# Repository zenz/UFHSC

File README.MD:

准备开源一个东西，用来控制地暖系统的。
市场上有类似的产品，但都是闭源的，这个开源，爱折腾爱研究爱写程序的，可以通过这个东西来设计和测试自己的地暖控制逻辑。

包含的接口有：
1、两路温度传感器接口（用B=3950，100K 精度1% NTC电阻温度传感器）
2、一路壁挂炉采暖启停控制接口
3、一路循环泵启停控制接口
4、一路负载式温控面板接口
5、一路温控面板直接控制的热电阀接口
6、一个UART通讯接口，用于通过USB2TTL接线实现与电脑串口通讯
7、一个ICSP接口，用于给单片机刷写Bootloader
8、一个ESP-05款无线WIFI模块接口，用于实现IoT监控
9、一个USB/AC供电跳针接口，用于选择单片机电源供给方式，调试用
10、一个预留的开关判断接口（目前在代码中用于是否连接循环泵的判断）

整个设备，全部采用直插式原件，方便爱好者自己焊接制作。所有用到的零件，都可以在网上（淘宝）购买到。
温度传感器精度可通过选择精度高的NTC电阻以及分压电阻(4.7K)来调节。
目前选用的NTC精度1%，分压电阻精度5%，测试下来在测试物温度恒定时，波动温度不超过0.2度（个人认为对地暖来说这个精度够了，波动更大的原因是开关电源的稳定性）。

单片机采用ATMEL公司的ATMEGA328P-PU，8位处理芯片，FLASH内存32K，动态内存2K，刷开源固件Arduino。
原始控制代码也全部开源，用Arduino编写，在Arduino IDE 1.0.5 以上版本编译通过并可通过USB2TTL上传到单片机。

开源的目的是什么？
个人一直是开源（软硬件）的支持者，认同开源可以使得在开放式讨论环境中，目标理论和算法能够得到更充分的探讨和完善。而且能够在使用环境适应性上有更加灵活的应对方法来解决实际的问题。FDM（熔融堆积成型）三维打印机这几年的发展就是一个例子。还有桌面CNC铣床GBRL，微型纺织机FirePicker等等。Github上随便搜搜都能找到一堆的开源软硬件项目。

开源会不会对企业带来经济损失？
个人认为这是一个伪命题。一个企业的研发能力是有限的，特别是中小型企业，要能够有人员和资金持续地，不断投入一个项目的研究还不钻牛角尖是很难的。因此，很多的企业，甚至是大企业，都采取部分开源的做法，来吸引更多对此问题关注的人参与进来，从而在获得的研究结果中提取有利于企业本身的数据和技术，来不断完善企业自己生产和销售的产品。产品做好了，买来使用的人其实占据了绝大多数。

开源需要的是什么？
开源需要的是真诚的交流和主动改变的心态，在这一点上，国外的开发者似乎比国内的做的要好一些。但这几年，国内的开源项目也多起来了。主要还是心态的慢慢转变吧。

接下来会怎么做？
我会把这个项目放到Github上，所有的设计文件，代码，让有想法又愿意分享并贡献的人可以跟进交流。希望这个开源项目能获得更多人的关注，从而使得对地面辐射采暖节能控制更多的了解和应用。这样我就成功了。如果最后也没有什么进步，那么我也至少努力过了。

OK，我要说的说完了。你约不约？

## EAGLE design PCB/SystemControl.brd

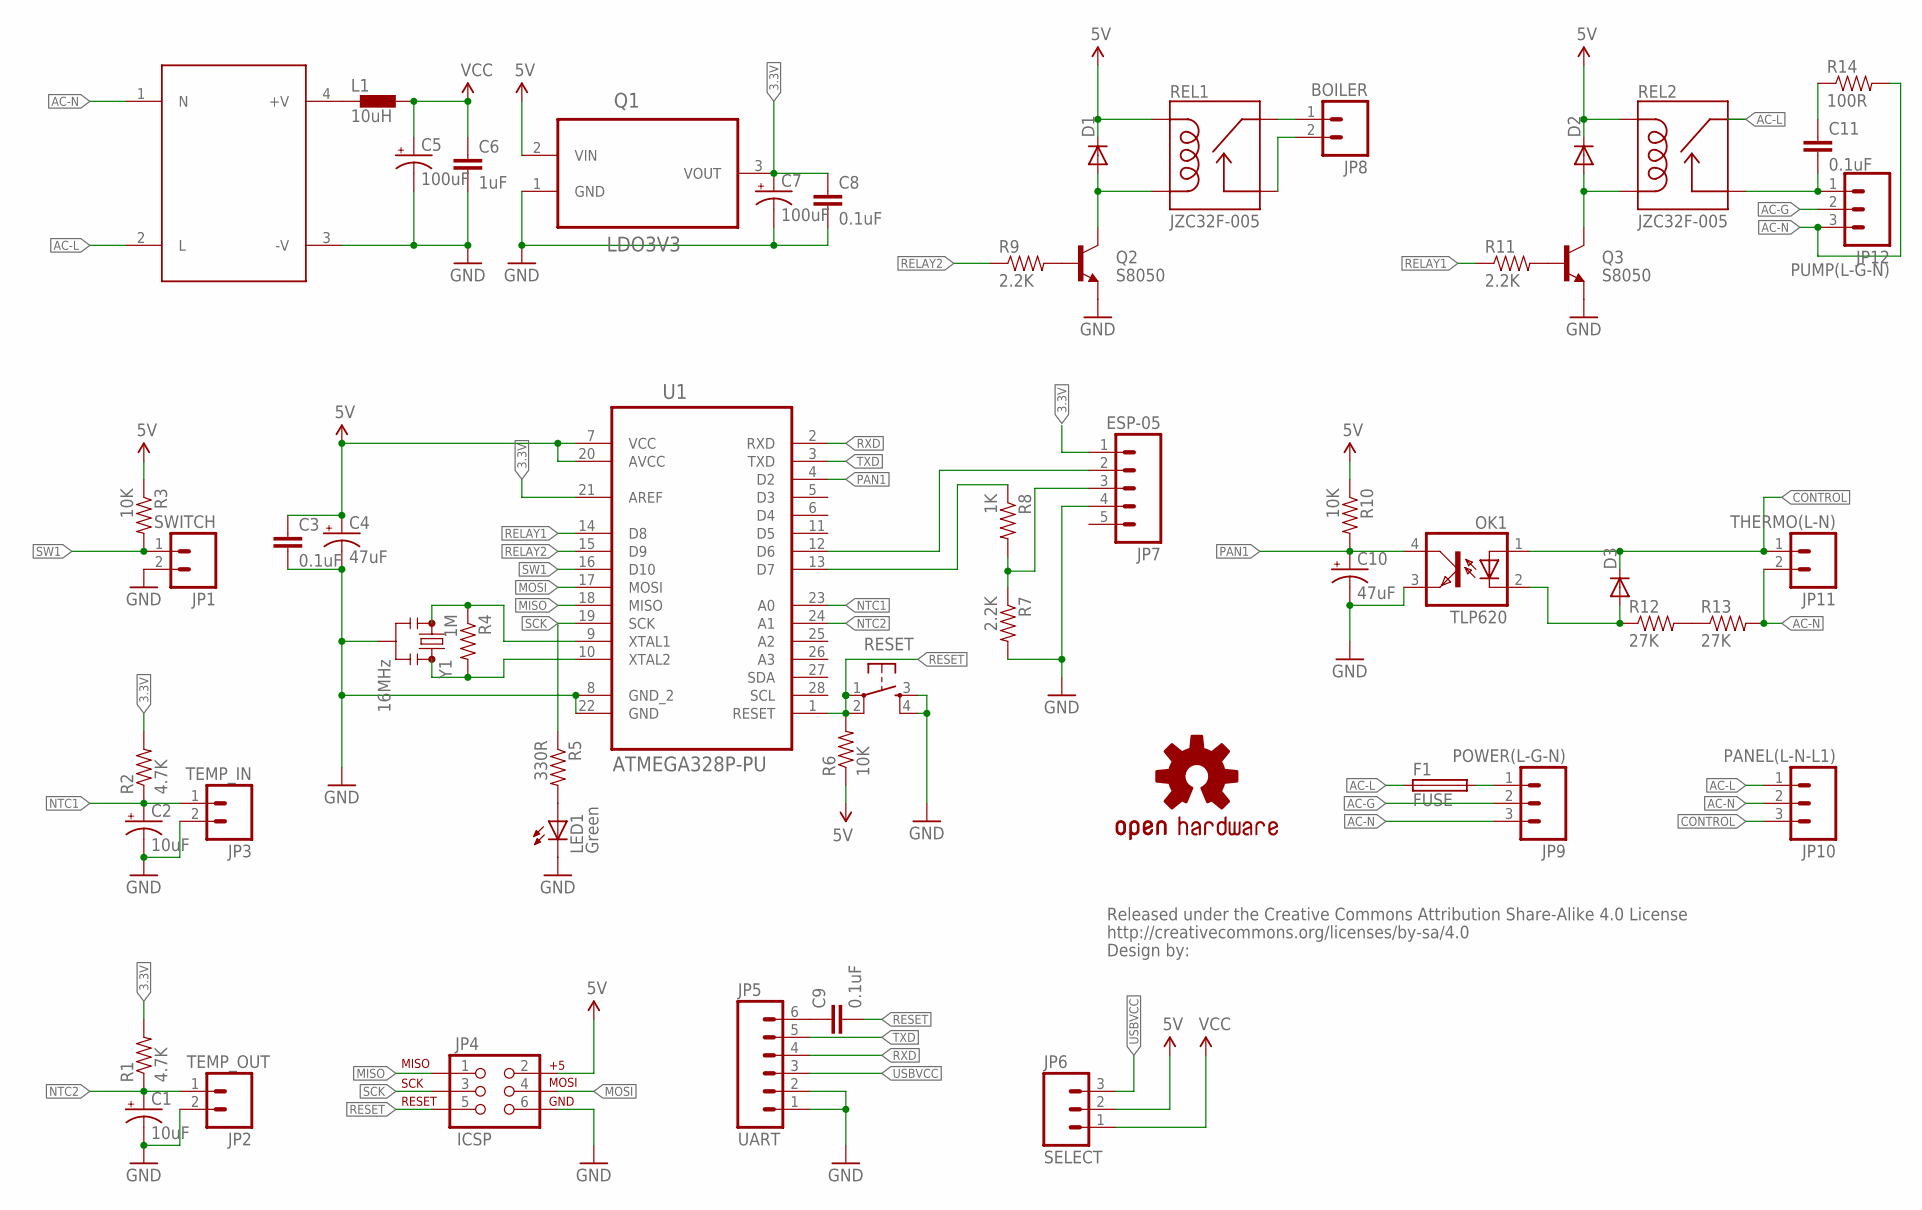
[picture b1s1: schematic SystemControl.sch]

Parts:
C1, C2: 10uF; CPOL-RADIAL-10UF-25V
C3, C8, C9: 0.1uF; CAP-PTH-SMALL2
C4, C10: 47uF; CPOL-RADIAL-10UF-25V
C5, C7: 100uF; CPOL-RADIAL-10UF-25V
C6: 1uF; CAP-PTH-SMALL2
C11: 0.1uF; CAP-PTH-LARGE
CC_TEXT1: CREATIVE_COMMONS
D1, D2, D3: 1N4007; DO-1N4148
F1: FUSE; SHK20L
IC1: NI-BOXING
JP1: SWITCH; 1X02_LOCK
JP2: TEMP_OUT; 1X02_LOCK
JP3: TEMP_IN; 1X02_LOCK
JP4: ICSP; 2X3
JP5: UART; 1X06_LOCK
JP6: SELECT; 1X03_LOCK
JP7: ESP-05; 1X05_LOCK
JP8: BOILER; SCREWTERMINAL-5MM-2
JP9: POWER(L-G-N); SCREWTERMINAL-5MM-3
JP10: PANEL(L-N-L1); SCREWTERMINAL-5MM-3
JP11: THERMO(L-N); SCREWTERMINAL-5MM-2
JP12: PUMP(L-G-N); SCREWTERMINAL-5MM-3
L1: 10uH; BL01RN1A
LED1: Green; LED3MM
LOGO1: OSHW-LOGOL; OSHW-LOGO-L
OK1: TLP620; DIL04
Q1: LDO3V3; TO127P254X533-3
Q2, Q3: S8050; TO-92
R1, R2: 4.7K; AXIAL-0.4
R3, R6, R10: 10K; AXIAL-0.4
R4: 1M; AXIAL-0.4
R5: 330R; AXIAL-0.4
R7, R9, R11: 2.2K; AXIAL-0.4
R8: 1K; AXIAL-0.4
R12, R13: 27K; AXIAL-0.6
R14: 100R; AXIAL-0.6
REL1, REL2: JZC32F-005; RELAY-JZC
RESET: TAC_SWITCHPTH; TACTILE-PTH
U1: ATMEGA328P-PU; DIP254P762X457-28
Y1: 16MHz; RESONATOR-PTH

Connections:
3.3V: C7.1 (+), C8.1, JP7.1, Q1.3 (VOUT), R1.P$2 (2), R2.P$2 (2), U1.21 (AREF)
5V: C3.1, C4.1 (+), D1.C, D2.C, JP4.2 (VCC), JP6.2, Q1.2 (VIN), R3.P$1 (1), R6.P$1 (1), R10.P$1 (1), REL1.5 (COIL1), REL2.5 (COIL1), U1.7 (VCC), U1.20 (AVCC)
AC-G: JP9.2, JP12.2
AC-L: F1.1A (1), IC1.2 (L), JP10.1, REL2.4 (MAIN)
AC-N: IC1.1 (N), JP9.3, JP10.2, JP11.2, JP12.3, R13.P$2 (2), R14.P$2 (2)
CONTROL: D3.C, JP10.3, JP11.1, OK1.1 (A)
GND: C1.2 (-), C2.2 (-), C3.2, C4.2 (-), C5.2 (-), C6.2, C7.2 (-), C8.2, C10.2 (-), IC1.3 (-V), JP1.2, JP2.2, JP3.2, JP4.6 (GND), JP5.1 (GND), JP5.2 (EMPTY), JP7.4, LED1.K (C), OK1.3 (EMIT), Q1.1 (GND), Q2.1 (E), Q3.1 (E), R7.P$2 (2), RESET.3, RESET.4, U1.8 (GND_2), U1.22 (GND), Y1.2
MISO: JP4.1 (MISO), U1.18 (MISO)
MOSI: JP4.4 (MOSI), U1.17 (MOSI)
unnamed: C9.1, JP5.6 (RESET)
unnamed: R4.P$1 (1), U1.9 (XTAL1), Y1.1
unnamed: R4.P$2 (2), U1.10 (XTAL2), Y1.3
unnamed: Q3.2 (B), R11.P$2 (2)
unnamed: D2.A, Q3.3 (C), REL2.1 (COIL2)
unnamed: Q2.2 (B), R9.P$2 (2)
unnamed: D1.A, Q2.3 (C), REL1.1 (COIL2)
unnamed: JP8.1, REL1.4 (MAIN)
unnamed: JP8.2, REL1.3 (NO)
unnamed: LED1.A, R5.P$2 (2)
unnamed: C11.2, JP12.1, REL2.3 (NO)
unnamed: IC1.4 (+V), L1.1
unnamed: C11.1, R14.P$1 (1)
unnamed: JP7.3, R7.P$1 (1), R8.P$2 (2)
unnamed: F1.2A (2), JP9.1
unnamed: R12.P$2 (2), R13.P$1 (1)
unnamed: D3.A, OK1.2 (C), R12.P$1 (1)
unnamed: JP7.2, U1.12 (D6)
unnamed: R8.P$1 (1), U1.13 (D7)
NTC1: C2.1 (+), JP3.1, R2.P$1 (1), U1.23 (A0)
NTC2: C1.1 (+), JP2.1, R1.P$1 (1), U1.24 (A1)
PAN1: C10.1 (+), OK1.4 (COL), R10.P$2 (2), U1.4 (D2)
RELAY1: R11.P$1 (1), U1.14 (D8)
RELAY2: R9.P$1 (1), U1.15 (D9)
RESET: C9.2, JP4.5 (RESET), R6.P$2 (2), RESET.1, RESET.2, U1.1 (RESET)
RXD: JP5.4 (RXD), U1.2 (RXD)
SCK: JP4.3 (SCK), R5.P$1 (1), U1.19 (SCK)
SW1: JP1.1, R3.P$2 (2), U1.16 (D10)
TXD: JP5.5 (TXD), U1.3 (TXD)
USBVCC: JP5.3 (VCC), JP6.3
VCC: C5.1 (+), C6.1, JP6.1, L1.2

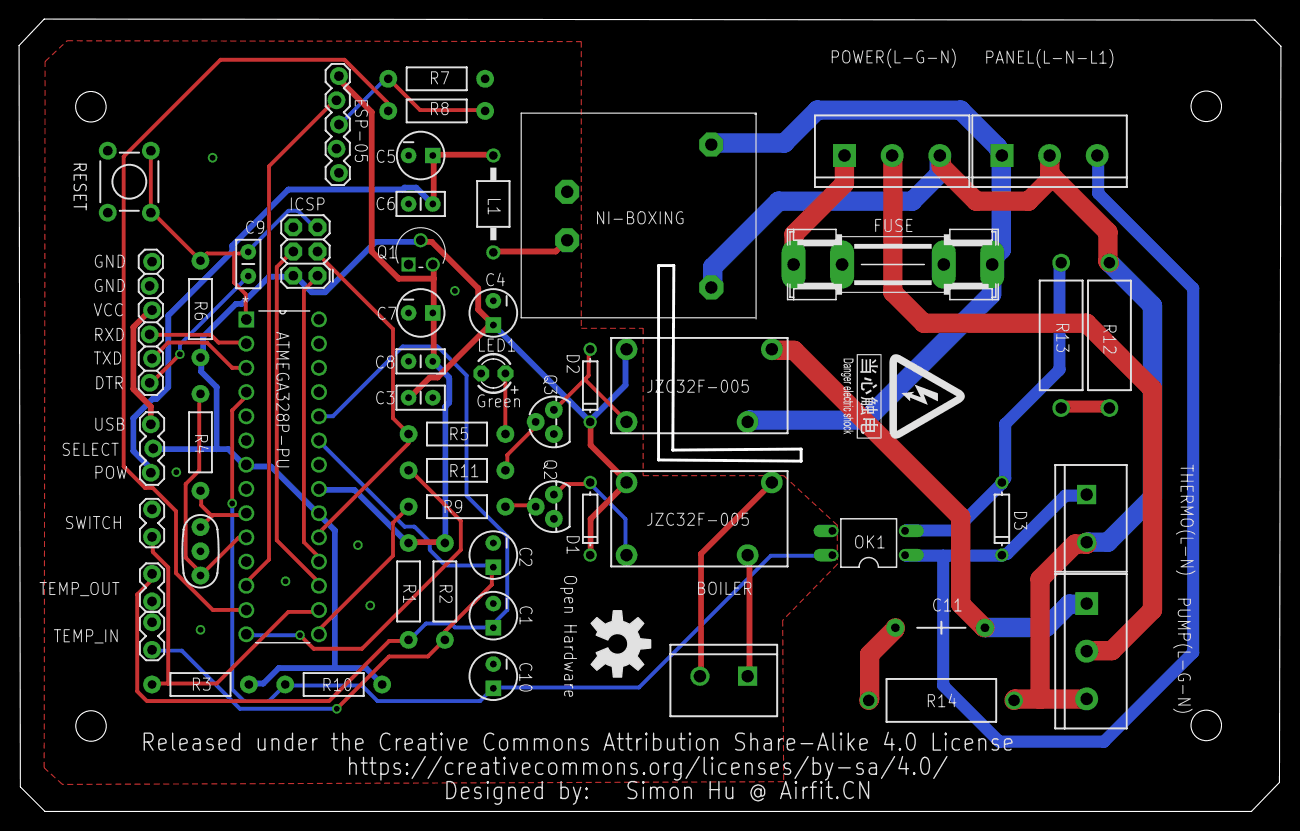
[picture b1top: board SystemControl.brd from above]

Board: 2 copper layers, 132.0 x 82.8 mm, 55 parts (0 on the bottom side), 40 nets.

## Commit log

2016-01-21 remove some unused files
2016-01-21 add a processing program to demo simple temperature ploting
2016-01-26 Add YeeLink test drive
2016-02-01 WiFi, 伪PID，伪线程
2016-02-03 修正显示编译选项的BUG

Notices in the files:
parts and their libraries:
SparkFun-Capacitors: Licensing: Creative Commons ShareAlike 4.0 International - https://creativecommons.org/licenses/by-sa/4.0
SparkFun-Retired: Released under the Creative Commons Attribution Share-Alike 4.0 License
SparkFun-Retired: https://creativecommons.org/licenses/by-sa/4.0
